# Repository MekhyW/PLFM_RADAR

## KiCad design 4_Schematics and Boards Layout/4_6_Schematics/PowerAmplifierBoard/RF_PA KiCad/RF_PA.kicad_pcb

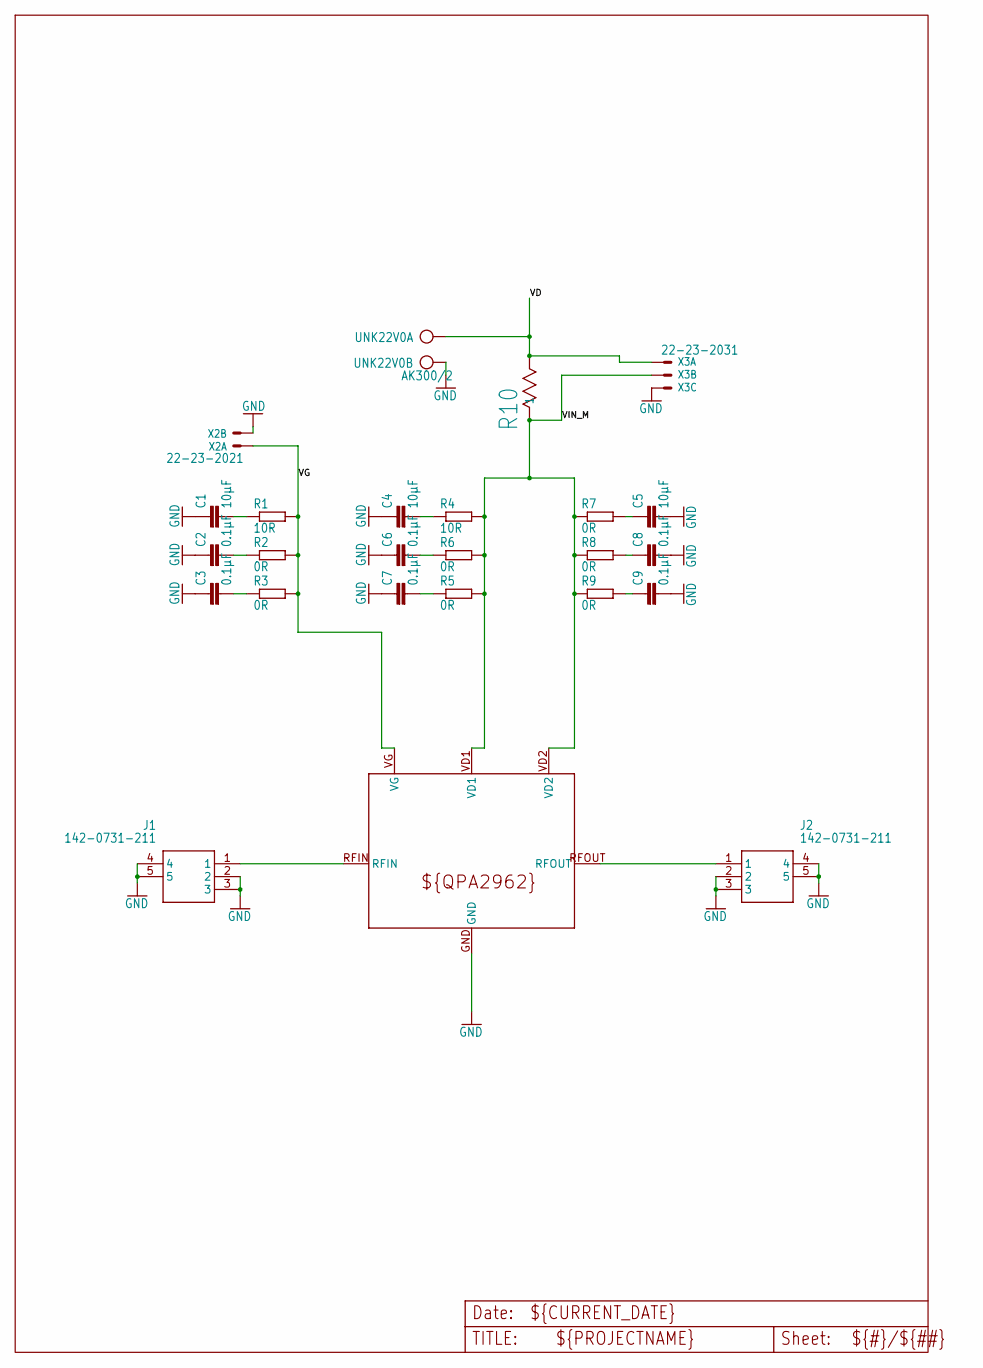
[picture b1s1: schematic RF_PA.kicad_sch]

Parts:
C1, C4, C5: 10µF; C1206
C2, C3, C6, C7, C8, C9: 0.1µF; C0402
J1, J2: 142-0731-211; 1420731211
R1, R4: 10R; R0402
R2, R3, R5, R7, R8, R9: 0R; R0402
R6: 0R; R0603
R10: 5mR; WSL2816_VIS
U$1: QPA2962_B
UNK22V0: AK300/2; AK300_2
X2: 22-23-2021
X3: 22-23-2031

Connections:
GND: C1.1, C2.1, C3.1, C4.1, C5.2, C6.1, C7.1, C8.2, C9.2, J1.2, J1.3, J1.4, J1.5, J2.2, J2.3, J2.4, J2.5, U$1.GND, UNK22V0.2, X2.2, X3.3
unnamed: C3.2, R3.1
unnamed: J1.1, U$1.RFIN
unnamed: C1.2, R1.1
unnamed: C2.2, R2.1
unnamed: C4.2, R4.1
unnamed: C6.2, R6.1
unnamed: C7.2, R5.1
unnamed: J2.1, U$1.RFOUT
unnamed: C5.1, R7.2
unnamed: C8.1, R8.2
unnamed: C9.1, R9.2
VD: R10.2, UNK22V0.1, X3.1
VG: R1.2, R2.2, R3.2, U$1.VG, X2.1
VIN_M: R4.2, R5.2, R6.2, R7.1, R8.1, R9.1, R10.1, U$1.VD1, U$1.VD2, X3.2

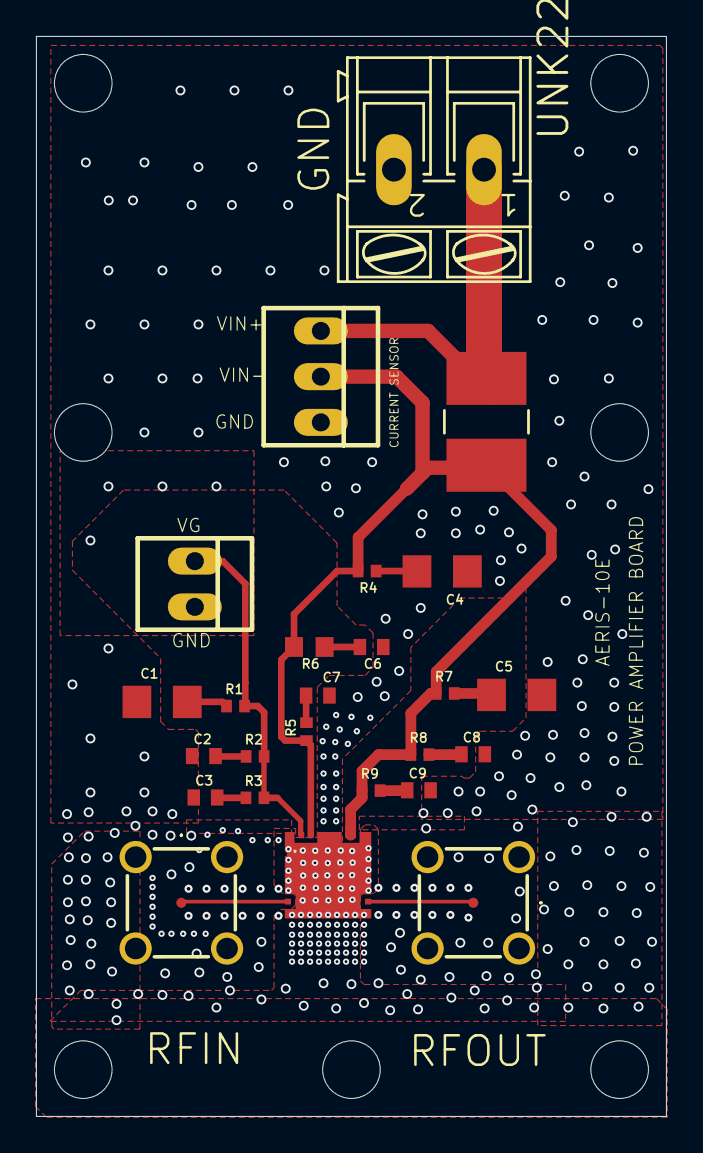
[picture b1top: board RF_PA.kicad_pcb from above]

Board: 4 copper layers, 35.0 x 60.0 mm, 32 parts (0 on the bottom side), 15 nets.

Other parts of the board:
UNK_HOLE_0: dummyfp0
UNK_HOLE_1: dummyfp1
UNK_HOLE_2: dummyfp2
UNK_HOLE_3: dummyfp3
UNK_HOLE_4: dummyfp4
UNK_HOLE_5: dummyfp5
UNK_HOLE_6: dummyfp6

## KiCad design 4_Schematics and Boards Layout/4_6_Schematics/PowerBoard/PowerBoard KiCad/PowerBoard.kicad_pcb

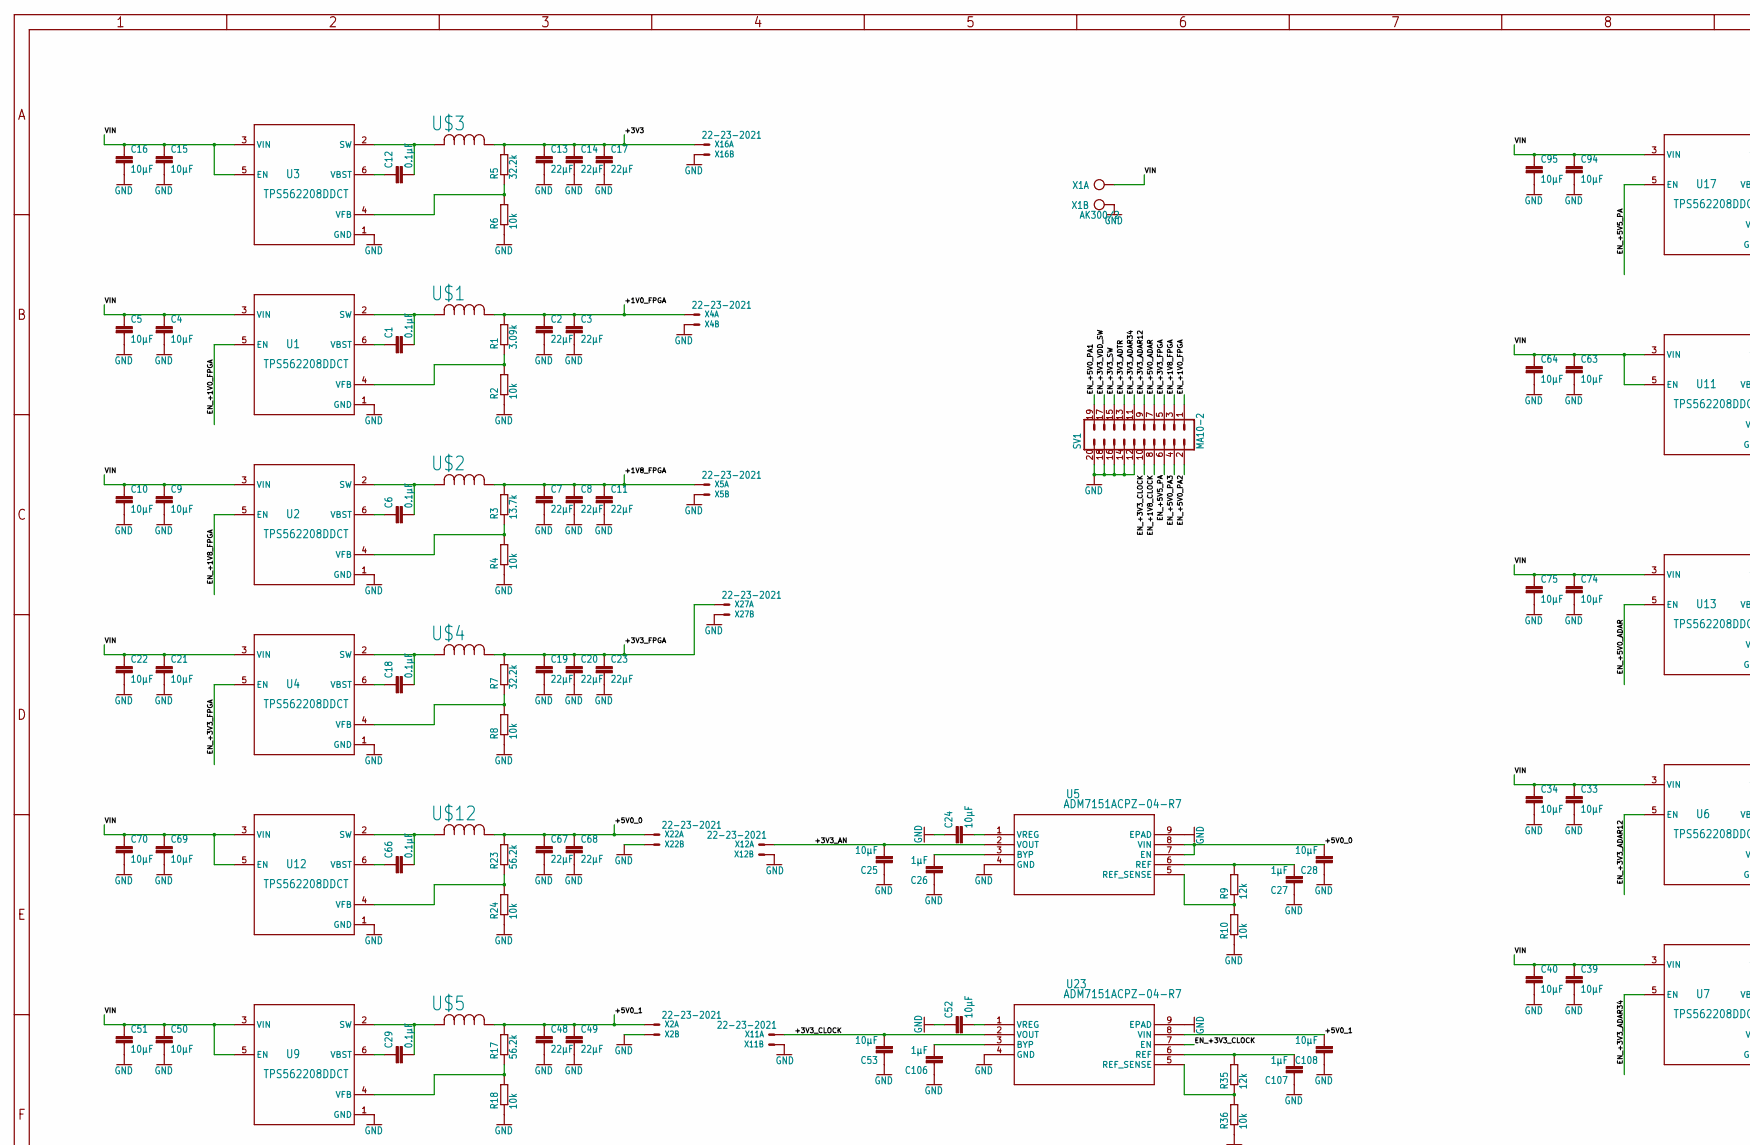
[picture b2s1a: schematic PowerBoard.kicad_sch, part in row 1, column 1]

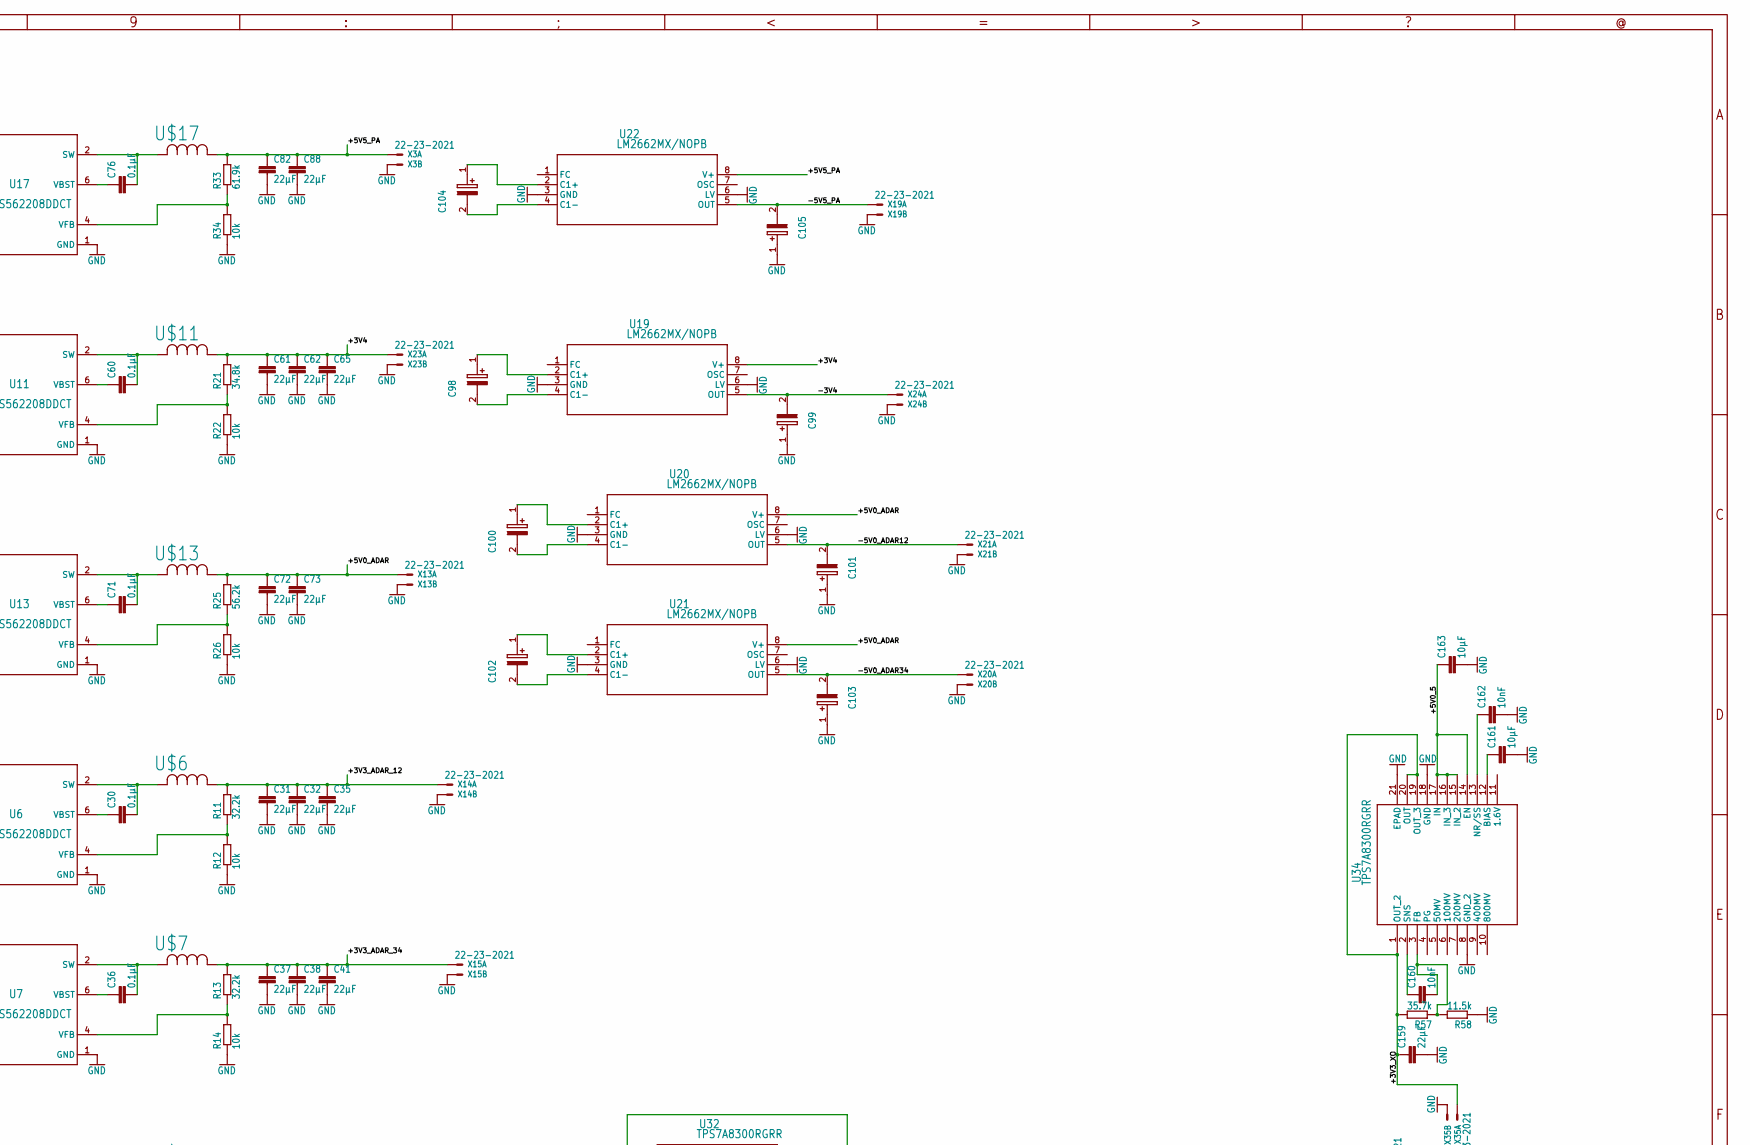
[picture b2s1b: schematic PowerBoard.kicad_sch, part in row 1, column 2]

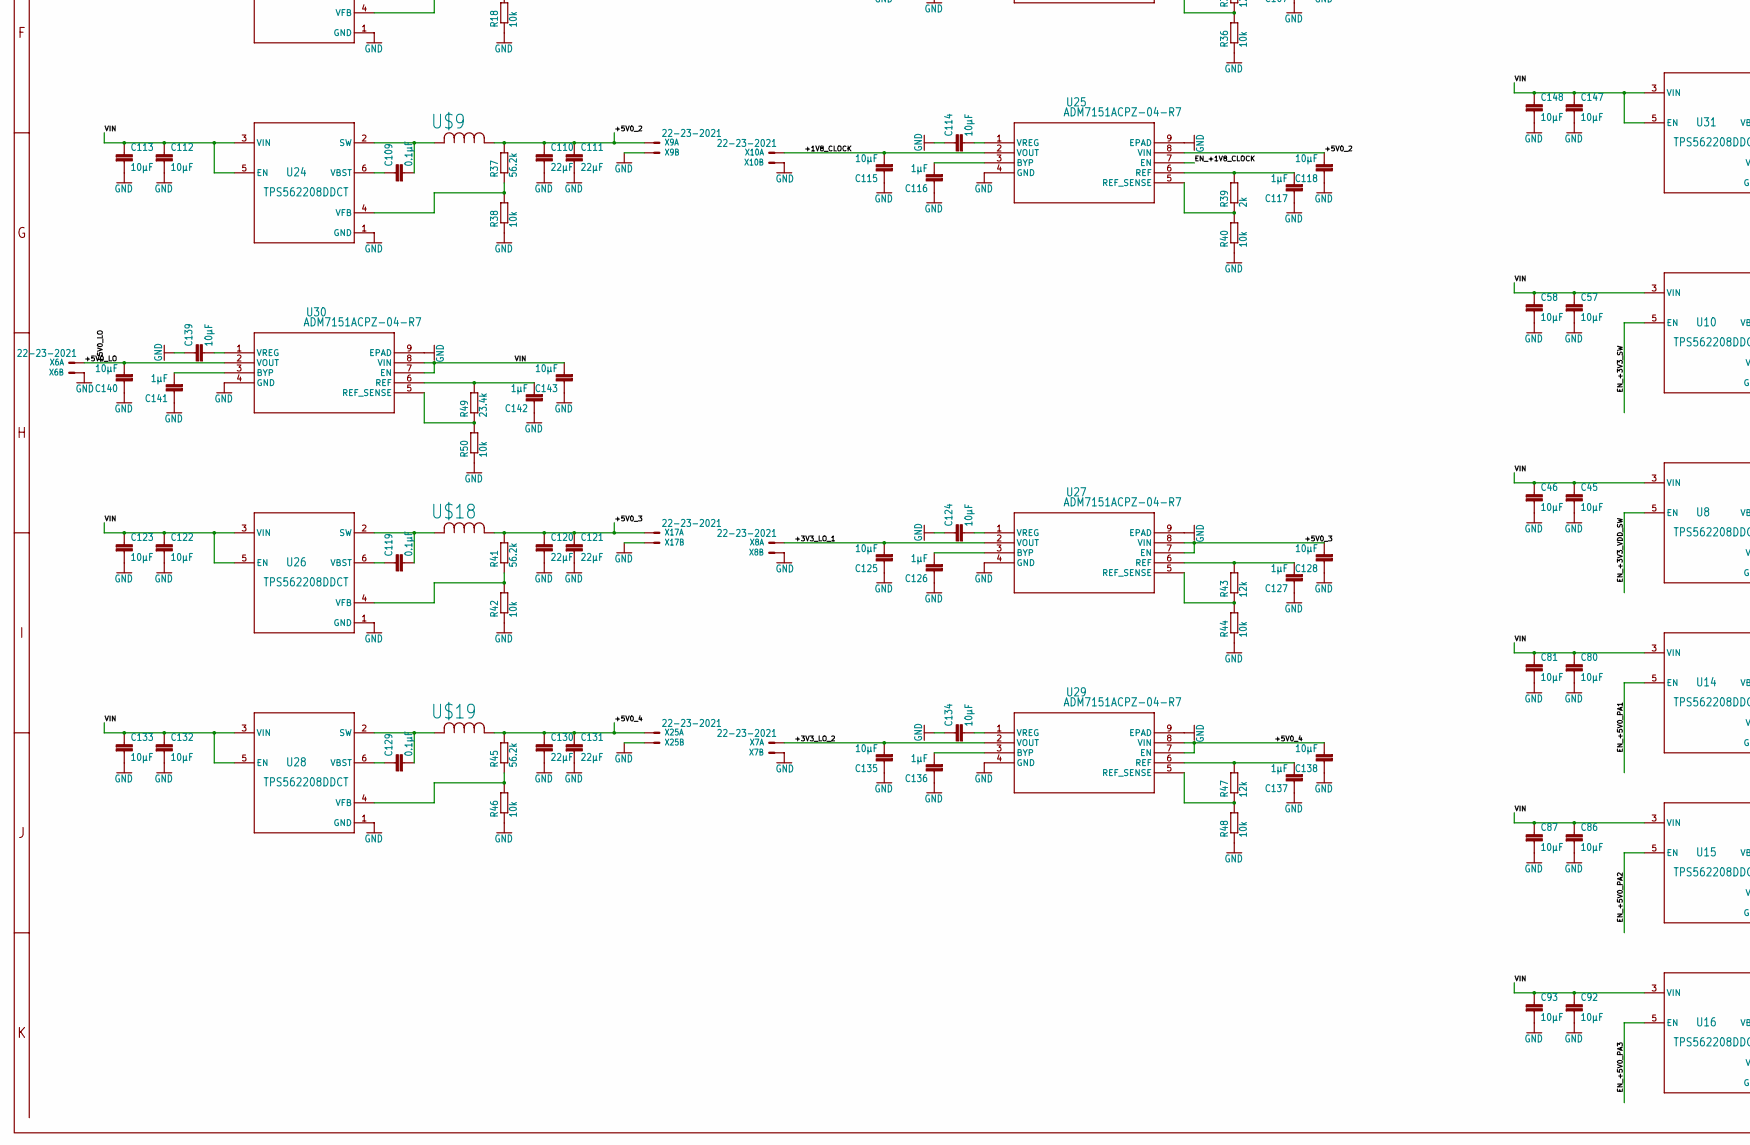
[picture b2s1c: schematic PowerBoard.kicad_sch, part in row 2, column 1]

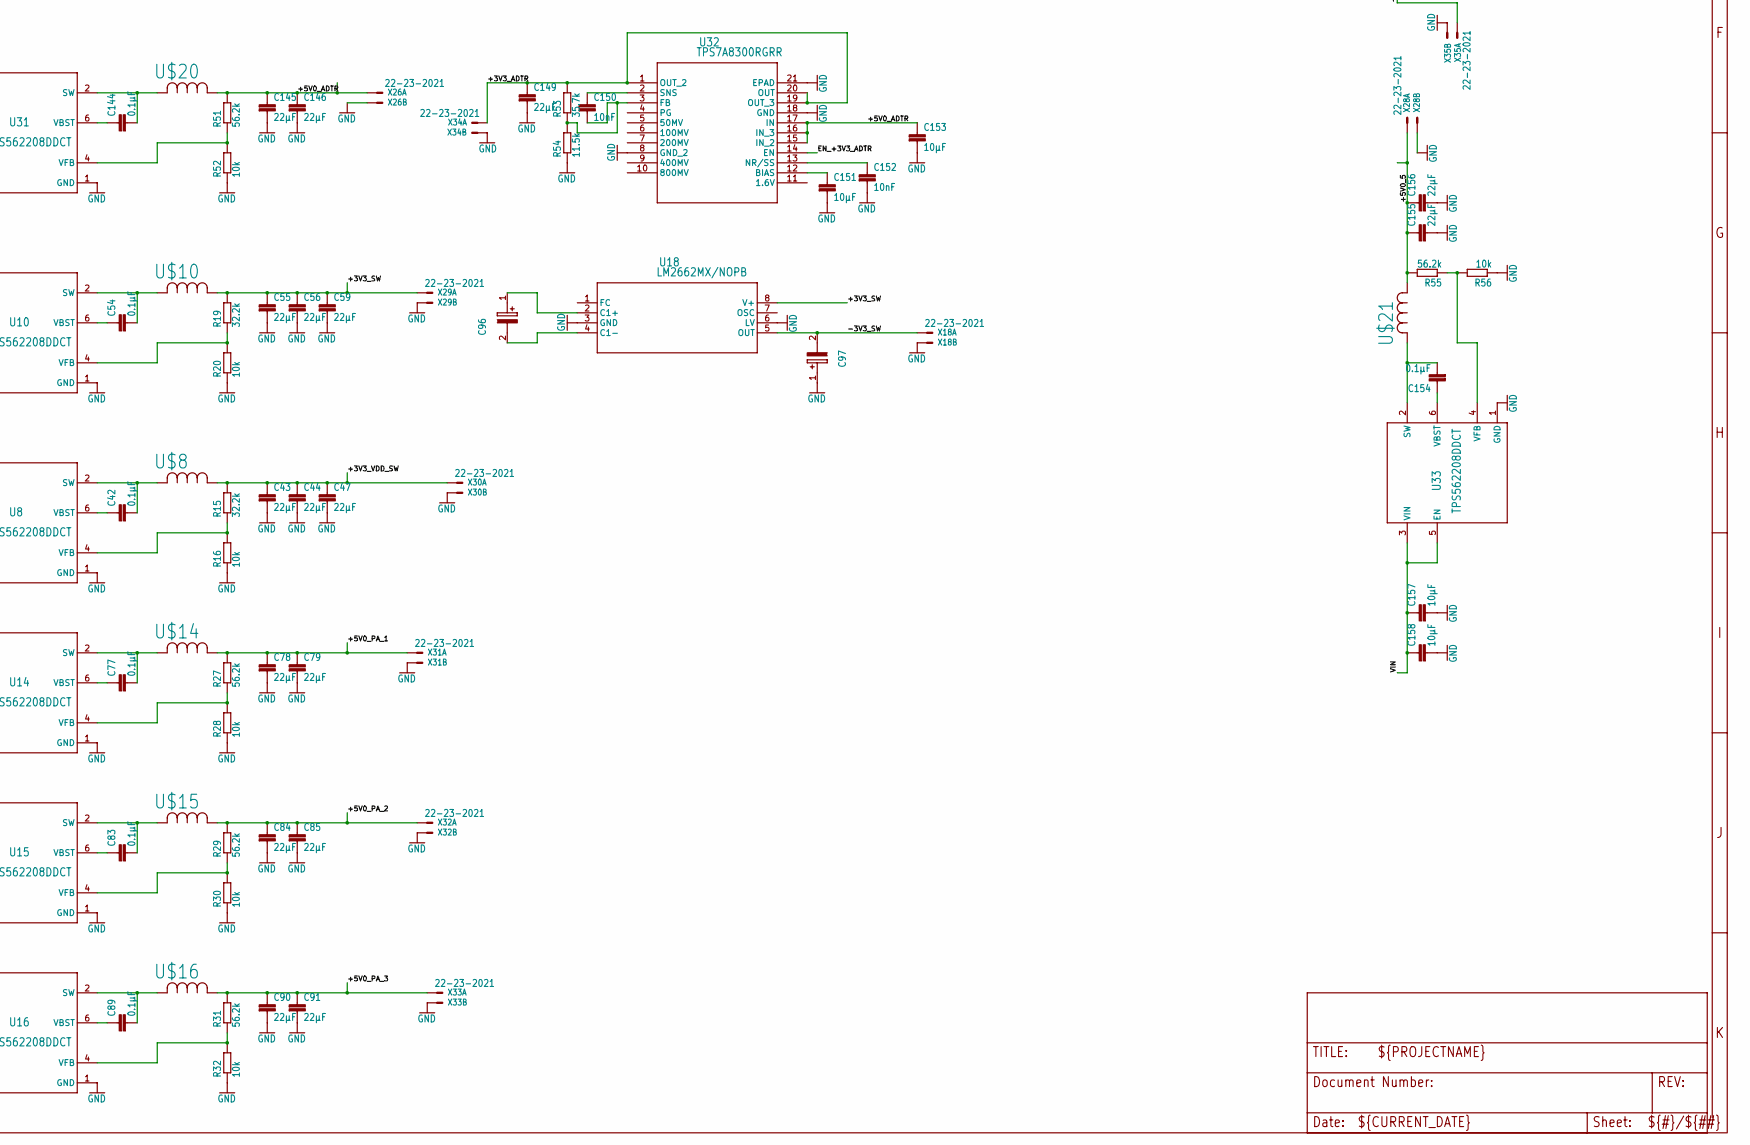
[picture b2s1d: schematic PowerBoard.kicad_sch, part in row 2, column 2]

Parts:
C1, C6, C12, C18, C29, C30, C36, C42, C54, C60, C66, C71, C76, C77, C83, C89, C109, C119, C129, C144, C154: 0.1µF; C0805
C2, C3, C7, C8, C11, C13, C14, C17, C19, C20, C23, C31, C32, C35, C37, C38, C41, C43, C44, C47, C48, C49, C55, C56, C59, C61, C62, C65, C67, C68, C72, C73, C78, C79, C82, C84, C85, C88, C90, C91, C110, C111, C120, C121, C130, C131, C145, C146, C149, C155, C156, C159: 22µF; C0603
C4, C5, C9, C10, C15, C16, C21, C22, C24, C25, C28, C33, C34, C39, C40, C45, C46, C50, C51, C52, C53, C57, C58, C63, C64, C69, C70, C74, C75, C80, C81, C86, C87, C92, C93, C94, C95, C108, C112, C113, C114, C115, C118, C122, C123, C124, C125, C128, C132, C133, C134, C135, C138, C139, C140, C143, C147, C148, C157, C158: 10µF; C0805
C26, C27, C106, C107, C116, C117, C126, C127, C136, C137, C141, C142: 1µF; C0805
C96, C97, C98, C99, C100, C101, C102, C103, C104, C105: T521W476M020ATE045; T521W
C150, C152, C160, C162: 10nF; C0603
C151, C153, C161, C163: 10µF; C0603
R1: 3.09k; M0805
R2, R4, R6, R8, R10, R12, R14, R16, R18, R20, R22, R24, R26, R28, R30, R32, R34, R36, R38, R40, R42, R44, R46, R48, R50, R52, R56: 10k; M0805
R3: 13.7k; M0805
R5, R7, R11, R13, R15, R19: 32.2k; M0805
R9, R35, R43, R47: 12k; M0805
R17, R23, R25, R27, R29, R31, R37, R41, R45, R51, R55: 56.2k; M0805
R21: 34.8k; M0805
R33: 61.9k; M0805
R39: 2k; M0805
R49: 23.4k; M0805
R53, R57: 35.7k; M0805
R54, R58: 11.5k; M0805
SV1: MA10-2
U1, U2, U3, U4, U6, U7, U8, U9, U10, U11, U12, U13, U14, U15, U16, U17, U24, U26, U28, U31, U33: TPS562208DDCT; DDC0006A_N
U5, U23, U25, U27, U29, U30: ADM7151ACPZ-04-R7; CP_8_11_ADI
U18, U19, U20, U21, U22: LM2662MX/NOPB; M08A
U32, U34: TPS7A8300RGRR; RGR20_2P05X2P05_TEX
U$1, U$2: 2.2µH; IND_VLP8040T-1R0N_TDK
U$3, U$4, U$5, U$6, U$7, U$8, U$9, U$10, U$11, U$12, U$13, U$14, U$15, U$16, U$17, U$18, U$19, U$20, U$21: 3.3µH; IND_VLP8040T-1R0N_TDK
X1: AK300/2; AK300_2
X2, X3, X4, X5, X6, X7, X8, X9, X10, X11, X12, X13, X14, X15, X16, X17, X18, X19, X20, X21, X22, X23, X24, X25, X26, X27, X28, X29, X30, X31, X32, X33, X34, X35: 22-23-2021

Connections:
+1V0_FPGA: C2.1, C3.1, R1.2, U$1.1, X4.1
+1V8_CLOCK: C115.2, U25.2 (VOUT), X10.1
+1V8_FPGA: C7.1, C8.1, C11.1, R3.2, U$2.1, X5.1
+3V3: C13.1, C14.1, C17.1, R5.2, U$3.1, X16.1
+3V3_ADAR_12: C31.1, C32.1, C35.1, R11.2, U$6.1, X14.1
+3V3_ADAR_34: C37.1, C38.1, C41.1, R13.2, U$7.1, X15.1
+3V3_ADTR: C149.1, R53.2, U32.1 (OUT_2), U32.19 (OUT_3), U32.20 (OUT), X34.1
+3V3_AN: C25.2, U5.2 (VOUT), X12.1
+3V3_CLOCK: C53.2, U23.2 (VOUT), X11.1
+3V3_FPGA: C19.1, C20.1, C23.1, R7.2, U$4.1, X27.1
+3V3_LO_1: C125.2, U27.2 (VOUT), X8.1
+3V3_LO_2: C135.2, U29.2 (VOUT), X7.1
+3V3_SW: C55.1, C56.1, C59.1, R19.2, U18.8 (V+), U$10.1, X29.1
+3V3_VDD_SW: C43.1, C44.1, C47.1, R15.2, U$8.1, X30.1
+3V3_XO: C159.1, R57.2, U34.1 (OUT_2), U34.19 (OUT_3), U34.20 (OUT), X35.1
+3V4: C61.1, C62.1, C65.1, R21.2, U19.8 (V+), U$11.1, X23.1
+5V0_0: C28.2, C67.1, C68.1, R23.2, U5.7 (EN), U5.8 (VIN), U$12.1, X22.1
+5V0_1: C48.1, C49.1, C108.2, R17.2, U23.8 (VIN), U$5.1, X2.1
+5V0_2: C110.1, C111.1, C118.2, R37.2, U25.8 (VIN), U$9.1, X9.1
+5V0_3: C120.1, C121.1, C128.2, R41.2, U27.7 (EN), U27.8 (VIN), U$18.1, X17.1
+5V0_4: C130.1, C131.1, C138.2, R45.2, U29.7 (EN), U29.8 (VIN), U$19.1, X25.1
+5V0_5: C155.1, C156.1, C163.1, R55.2, U34.14 (EN), U34.15 (IN_2), U34.16 (IN_3), U34.17 (IN), U$21.1, X28.1
+5V0_ADAR: C72.1, C73.1, R25.2, U20.8 (V+), U21.8 (V+), U$13.1, X13.1
+5V0_ADTR: C145.1, C146.1, C153.1, R51.2, U32.15 (IN_2), U32.16 (IN_3), U32.17 (IN), U$20.1, X26.1
+5V0_LO: C140.2, U30.2 (VOUT), X6.1; also elsewhere on the board
+5V0_PA_1: C78.1, C79.1, R27.2, U$14.1, X31.1
+5V0_PA_2: C84.1, C85.1, R29.2, U$15.1, X32.1
+5V0_PA_3: C90.1, C91.1, R31.2, U$16.1, X33.1
+5V5_PA: C82.1, C88.1, R33.2, U22.8 (V+), U$17.1, X3.1
-3V3_SW: C97.2 (-), U18.5 (OUT), X18.1
-3V4: C99.2 (-), U19.5 (OUT), X24.1
-5V0_ADAR12: C101.2 (-), U20.5 (OUT), X21.1
-5V0_ADAR34: C103.2 (-), U21.5 (OUT), X20.1
-5V5_PA: C105.2 (-), U22.5 (OUT), X19.1
EN_+1V0_FPGA: SV1.1, U1.5 (EN)
EN_+1V8_CLOCK: SV1.8, U25.7 (EN)
EN_+1V8_FPGA: SV1.3, U2.5 (EN)
EN_+3V3_ADAR12: SV1.9, U6.5 (EN)
EN_+3V3_ADAR34: SV1.11, U7.5 (EN)
EN_+3V3_ADTR: SV1.13, U32.14 (EN)
EN_+3V3_CLOCK: SV1.10, U23.7 (EN)
EN_+3V3_FPGA: SV1.5, U4.5 (EN)
EN_+3V3_SW: SV1.15, U10.5 (EN)
EN_+3V3_VDD_SW: SV1.17, U8.5 (EN)
EN_+5V0_ADAR: SV1.7, U13.5 (EN)
EN_+5V0_PA1: SV1.19, U14.5 (EN)
EN_+5V0_PA2: SV1.2, U15.5 (EN)
EN_+5V0_PA3: SV1.4, U16.5 (EN)
EN_+5V5_PA: SV1.6, U17.5 (EN)
GND: C2.2, C3.2, C4.2, C5.2, C7.2, C8.2, C9.2, C10.2, C11.2, C13.2, C14.2, C15.2, C16.2, C17.2, C19.2, C20.2, C21.2, C22.2, C23.2, C24.1, C25.1, C26.1, C27.1, C28.1, C31.2, C32.2, C33.2, C34.2, C35.2, C37.2, C38.2, C39.2, C40.2, C41.2, C43.2, C44.2, C45.2, C46.2, C47.2, C48.2, C49.2, C50.2, C51.2, C52.1, C53.1, C55.2, C56.2, C57.2, C58.2, C59.2, C61.2, C62.2, C63.2, C64.2, C65.2, C67.2, C68.2, C69.2, C70.2, C72.2, C73.2, C74.2, C75.2, C78.2, C79.2, C80.2, C81.2, C82.2, C84.2, C85.2, C86.2, C87.2, C88.2, C90.2, C91.2, C92.2, C93.2, C94.2, C95.2, C97.1 (+), C99.1 (+), C101.1 (+), C103.1 (+), C105.1 (+), C106.1, C107.1, C108.1, C110.2, C111.2, C112.2, C113.2, C114.1, C115.1, C116.1, C117.1, C118.1, C120.2, C121.2, C122.2, C123.2, C124.1, C125.1, C126.1, C127.1, C128.1, C130.2, C131.2, C132.2, C133.2, C134.1, C135.1, C136.1, C137.1, C138.1, C139.1, C140.1, C141.1, C142.1, C143.1, C145.2, C146.2, C147.2, C148.2, C149.2, C151.2, C152.2, C153.2, C155.2, C156.2, C157.2, C158.2, C159.2, C161.2, C162.2, C163.2, R2.1, R4.1, R6.1, R8.1, R10.1, R12.1, R14.1, R16.1, R18.1, R20.1, R22.1, R24.1, R26.1, R28.1, R30.1, R32.1, R34.1, R36.1, R38.1, R40.1, R42.1, R44.1, R46.1, R48.1, R50.1, R52.1, R54.1, R56.1, R58.1, SV1.12, SV1.14, SV1.16, SV1.18, SV1.20, U1.1 (GND), U2.1 (GND), U3.1 (GND), U4.1 (GND), U5.4 (GND), U5.9 (EPAD), U6.1 (GND), U7.1 (GND), U8.1 (GND), U9.1 (GND), U10.1 (GND), U11.1 (GND), U12.1 (GND), U13.1 (GND), U14.1 (GND), U15.1 (GND), U16.1 (GND), U17.1 (GND), U18.3 (GND), U18.6 (LV), U19.3 (GND), U19.6 (LV), U20.3 (GND), U20.6 (LV), U21.3 (GND), U21.6 (LV), U22.3 (GND), U22.6 (LV), U23.4 (GND), U23.9 (EPAD), U24.1 (GND), U25.4 (GND), U25.9 (EPAD), U26.1 (GND), U27.4 (GND), U27.9 (EPAD), U28.1 (GND), U29.4 (GND), U29.9 (EPAD), U30.4 (GND), U30.9 (EPAD), U31.1 (GND), U32.8 (GND_2), U32.18 (GND), U32.21 (EPAD), U33.1 (GND), U34.8 (GND_2), U34.18 (GND), U34.21 (EPAD), X1.2, X2.2, X3.2, X4.2, X5.2, X6.2, X7.2, X8.2, X9.2, X10.2, X11.2, X12.2, X13.2, X14.2, X15.2, X16.2, X17.2, X18.2, X19.2, X20.2, X21.2, X22.2, X23.2, X24.2, X25.2, X26.2, X27.2, X28.2, X29.2, X30.2, X31.2, X32.2, X33.2, X34.2, X35.2; also elsewhere on the board
unnamed: C1.2, U1.2 (SW), U$1.2
unnamed: C1.1, U1.6 (VBST)
unnamed: C6.2, U2.2 (SW), U$2.2
unnamed: R1.1, R2.2, U1.4 (VFB)
unnamed: C6.1, U2.6 (VBST)
unnamed: R3.1, R4.2, U2.4 (VFB)
unnamed: C12.2, U3.2 (SW), U$3.2
unnamed: C12.1, U3.6 (VBST)
unnamed: R5.1, R6.2, U3.4 (VFB)
unnamed: C18.2, U4.2 (SW), U$4.2
unnamed: C18.1, U4.6 (VBST)
unnamed: R7.1, R8.2, U4.4 (VFB)
unnamed: C24.2, U5.1 (VREG)
unnamed: C139.2, U30.1 (VREG)
unnamed: C26.2, U5.3 (BYP)
unnamed: C30.2, U6.2 (SW), U$6.2
unnamed: C30.1, U6.6 (VBST)
unnamed: R11.1, R12.2, U6.4 (VFB)
unnamed: C36.2, U7.2 (SW), U$7.2
unnamed: C36.1, U7.6 (VBST)
unnamed: R13.1, R14.2, U7.4 (VFB)
unnamed: C42.2, U8.2 (SW), U$8.2
unnamed: C42.1, U8.6 (VBST)
unnamed: R15.1, R16.2, U8.4 (VFB)
unnamed: R9.1, R10.2, U5.5 (REF_SENSE)
unnamed: C29.2, U9.2 (SW), U$5.2
unnamed: C27.2, R9.2, U5.6 (REF)
unnamed: C54.2, U10.2 (SW), U$10.2
unnamed: C54.1, U10.6 (VBST)
unnamed: R19.1, R20.2, U10.4 (VFB)
unnamed: C60.2, U11.2 (SW), U$11.2
unnamed: C60.1, U11.6 (VBST)
unnamed: R21.1, R22.2, U11.4 (VFB)
unnamed: C66.2, U12.2 (SW), U$12.2
unnamed: C66.1, U12.6 (VBST)
unnamed: R23.1, R24.2, U12.4 (VFB)
unnamed: C71.2, U13.2 (SW), U$13.2
unnamed: C71.1, U13.6 (VBST)
unnamed: R25.1, R26.2, U13.4 (VFB)
unnamed: C77.2, U14.2 (SW), U$14.2
unnamed: C77.1, U14.6 (VBST)
unnamed: R27.1, R28.2, U14.4 (VFB)
unnamed: C83.2, U15.2 (SW), U$15.2
unnamed: C83.1, U15.6 (VBST)
unnamed: R29.1, R30.2, U15.4 (VFB)
unnamed: C89.2, U16.2 (SW), U$16.2
unnamed: C89.1, U16.6 (VBST)
unnamed: R31.1, R32.2, U16.4 (VFB)
unnamed: C76.2, U17.2 (SW), U$17.2
unnamed: C76.1, U17.6 (VBST)
unnamed: R33.1, R34.2, U17.4 (VFB)
unnamed: C98.1 (+), U19.2 (C1+)
unnamed: C98.2 (-), U19.4 (C1-)
unnamed: C96.1 (+), U18.2 (C1+)
unnamed: C96.2 (-), U18.4 (C1-)
unnamed: C100.1 (+), U20.2 (C1+)
unnamed: C100.2 (-), U20.4 (C1-)
unnamed: C102.1 (+), U21.2 (C1+)
unnamed: C102.2 (-), U21.4 (C1-)
unnamed: C104.1 (+), U22.2 (C1+)
unnamed: C104.2 (-), U22.4 (C1-)
unnamed: C141.2, U30.3 (BYP)
unnamed: R49.1, R50.2, U30.5 (REF_SENSE)
unnamed: C29.1, U9.6 (VBST)
unnamed: R17.1, R18.2, U9.4 (VFB)
unnamed: C52.2, U23.1 (VREG)
unnamed: C142.2, R49.2, U30.6 (REF)
unnamed: C106.2, U23.3 (BYP)
unnamed: R35.1, R36.2, U23.5 (REF_SENSE)
unnamed: C107.2, R35.2, U23.6 (REF)
unnamed: C144.2, U31.2 (SW), U$20.2
unnamed: C144.1, U31.6 (VBST)
unnamed: C109.2, U24.2 (SW), U$9.2
unnamed: C109.1, U24.6 (VBST)
unnamed: R37.1, R38.2, U24.4 (VFB)
unnamed: C114.2, U25.1 (VREG)
unnamed: R51.1, R52.2, U31.4 (VFB)
unnamed: C116.2, U25.3 (BYP)
unnamed: R39.1, R40.2, U25.5 (REF_SENSE)
unnamed: C117.2, R39.2, U25.6 (REF)
unnamed: C154.2, U33.2 (SW), U$21.2
unnamed: C150.1, U32.2 (SNS)
unnamed: C119.2, U26.2 (SW), U$18.2
unnamed: C119.1, U26.6 (VBST)
unnamed: R41.1, R42.2, U26.4 (VFB)
unnamed: C124.2, U27.1 (VREG)
unnamed: C154.1, U33.6 (VBST)
unnamed: C126.2, U27.3 (BYP)
unnamed: R43.1, R44.2, U27.5 (REF_SENSE)
unnamed: C127.2, R43.2, U27.6 (REF)
unnamed: C150.2, R53.1, R54.2, U32.3 (FB)
unnamed: C151.1, U32.12 (BIAS)
unnamed: C129.2, U28.2 (SW), U$19.2
unnamed: C129.1, U28.6 (VBST)
unnamed: R45.1, R46.2, U28.4 (VFB)
unnamed: C134.2, U29.1 (VREG)
unnamed: R55.1, R56.2, U33.4 (VFB)
unnamed: C136.2, U29.3 (BYP)
unnamed: R47.1, R48.2, U29.5 (REF_SENSE)
unnamed: C137.2, R47.2, U29.6 (REF)
unnamed: C152.1, U32.13 (NR/SS)
unnamed: C160.1, U34.2 (SNS)
unnamed: C160.2, R57.1, R58.2, U34.3 (FB)
unnamed: C161.1, U34.12 (BIAS)
unnamed: C162.1, U34.13 (NR/SS)
VIN: C4.1, C5.1, C9.1, C10.1, C15.1, C16.1, C21.1, C22.1, C33.1, C34.1, C39.1, C40.1, C45.1, C46.1, C50.1, C51.1, C57.1, C58.1, C63.1, C64.1, C69.1, C70.1, C74.1, C75.1, C80.1, C81.1, C86.1, C87.1, C92.1, C93.1, C94.1, C95.1, C112.1, C113.1, C122.1, C123.1, C132.1, C133.1, C143.2, C147.1, C148.1, C157.1, C158.1, U1.3 (VIN), U2.3 (VIN), U3.3 (VIN), U3.5 (EN), U4.3 (VIN), U6.3 (VIN), U7.3 (VIN), U8.3 (VIN), U9.3 (VIN), U9.5 (EN), U10.3 (VIN), U11.3 (VIN), U11.5 (EN), U12.3 (VIN), U12.5 (EN), U13.3 (VIN), U14.3 (VIN), U15.3 (VIN), U16.3 (VIN), U17.3 (VIN), U24.3 (VIN), U24.5 (EN), U26.3 (VIN), U26.5 (EN), U28.3 (VIN), U28.5 (EN), U30.7 (EN), U30.8 (VIN), U31.3 (VIN), U31.5 (EN), U33.3 (VIN), U33.5 (EN), X1.1

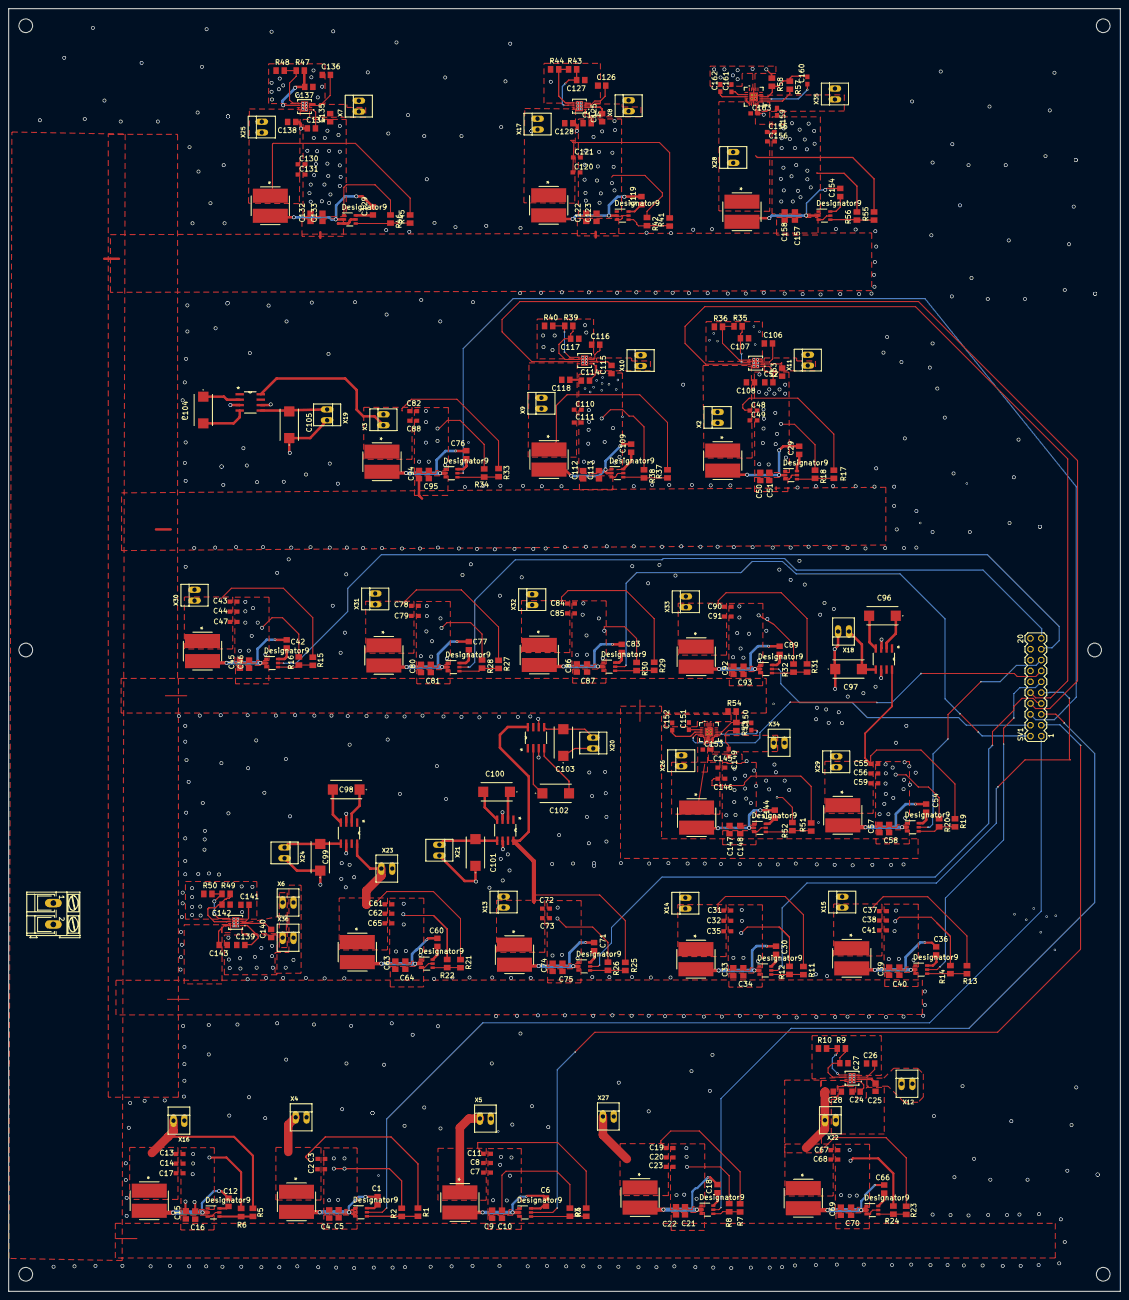
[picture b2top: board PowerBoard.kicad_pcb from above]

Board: 2 copper layers, 260.0 x 300.0 mm, 319 parts (0 on the bottom side), 156 nets.

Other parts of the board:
UNK_HOLE_0: dummyfp0
UNK_HOLE_1: dummyfp1
UNK_HOLE_2: dummyfp2
UNK_HOLE_3: dummyfp3
UNK_HOLE_4: dummyfp4
UNK_HOLE_5: dummyfp5
X36: 22-23-2021

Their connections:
+5V0_LO: X36.1; also elsewhere on the board
GND: X36.2; also elsewhere on the board

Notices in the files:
9_Firmware/9_1_Microcontroller/9_1_3_C_Cpp_Code/main.cpp:
Copyright (c) 2025 STMicroelectronics.
All rights reserved.
This software is licensed under terms that can be found in the LICENSE file
